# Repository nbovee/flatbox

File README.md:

# Flatbox: Low profile hitbox-layout fightstick

This repository contains 3D-printable models, PCB design files and code needed to make an arcade controller that looks like this:

There are five major versions of the Flatbox. As this is a fork, the three I do not have modifications planned for have been dropped, find them [here](https://github.com/jfedor2/flatbox). They all use Kailh low profile (choc v1) mechanical keyboard switches. The table below lists their main features. See the README for each version for details on how to make them.

version | [rev4](rev4b-pcb) | [rev5B](rev5b-pcb)
------- | --------------------- | ---------------------
case dimensions | 218x130x10mm | 218x126x10mm
compatibility (using provided firmware) | PC, PS3 | PC, PS3
add-on board | - | [RP2040-Zero](https://www.waveshare.com/rp2040-zero.htm)
onboard chip | RP2040 | - 
port | USB-C | USB-C
SMT assembly required | yes | no
firmware | [RP2040](firmware-rp2040) | [RP2040](firmware-rp2040)

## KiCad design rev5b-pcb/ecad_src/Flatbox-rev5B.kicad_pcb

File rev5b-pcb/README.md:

# Flatbox rev5B

This is rev5B of the Flatbox. In this version an [RP2040-Zero](https://www.waveshare.com/rp2040-zero.htm) board is soldered onto the main PCB.
In this version L3 & R3 have been relocated to allow for usage during play (bindable macro's like MK+HK, burst, taunt, etc). 

To make one you will need:

* [3D printed case parts](../case-manufacturing-files) - Select a top and bottom. Two colors tops are available if you have a capable printer.
* [the Flatbox 5B PCB](manufacturing-files)

* [RP2040-Zero](https://www.waveshare.com/rp2040-zero.htm)

* 12-14x Kailh low profile (choc v1) switches of your choice
* (optionally) 12x Kailh low profile hotswap sockets
* [3D printed buttoncaps](../manufacturing-files/3d-printed-buttoncaps)
* 4-6x 6x6x5mm tact switches

* 7x M3x6 flat head screws
* some kind of rubber feet or non-slip padding for the bottom
* a soldering iron

I printed the case at 0.20mm layer height. The top part should be printed upside-down, the bottom part should be printed as-is. They don't require supports.

The PCB can be ordered from a number of online services using the included [Gerber files](manufacturing-files), I used [JLCPCB](https://jlcpcb.com/) (leave all the settings at default, you can choose the PCB color). PCB thickness should be 1.6mm.

The switches can be soldered in directly to the PCB or you can use hotswap sockets. If you want to use hotswap sockets, you will have to print the appropriate bottom part of the case (it's 1mm thicker).

Solder the jumpers for L3 & R3 at the locations they will be used (jumpers are located on the rear of the board).

For the firmware you probably want to use [GP2040-CE](https://gp2040-ce.info/). Go to the [GP2040-CE downloads page](https://gp2040-ce.info/#/download) and get the UF2 file for Flatbox rev5. Do not get the file for the Waveshare RP2040-Zero, even though your stick uses it (it has a different pinout).

To flash the firmware, connect the board to a computer with a USB cable, then press the RESET button while holding the BOOT button on the RP2040-Zero. A drive named "RPI-RP2" should appear. Copy the UF2 file you downloaded to that drive. That's it.

(Of course you can also use any other RP2040-compatible firmware if you want.)

To flash the firmware, connect the board to a computer with a USB cable, then press the RESET button while holding the BOOT button on the RP2040-Zero. A drive named "RPI-RP2" should appear. Copy the [flatbox-rev5.uf2](firmware/flatbox-rev5.uf2) file to that drive. That's it.

PCB design licensed under [CC BY-SA 4.0](https://creativecommons.org/licenses/by-sa/4.0/).

PCB design uses the following:

* [keyswitches.pretty](https://github.com/daprice/keyswitches.pretty) by [daprice](https://github.com/daprice) ([CC BY-SA 4.0](https://creativecommons.org/licenses/by-sa/4.0/))
* RP2040-Zero STEP file downloaded from [Waveshare wiki](https://www.waveshare.com/wiki/RP2040-Zero)

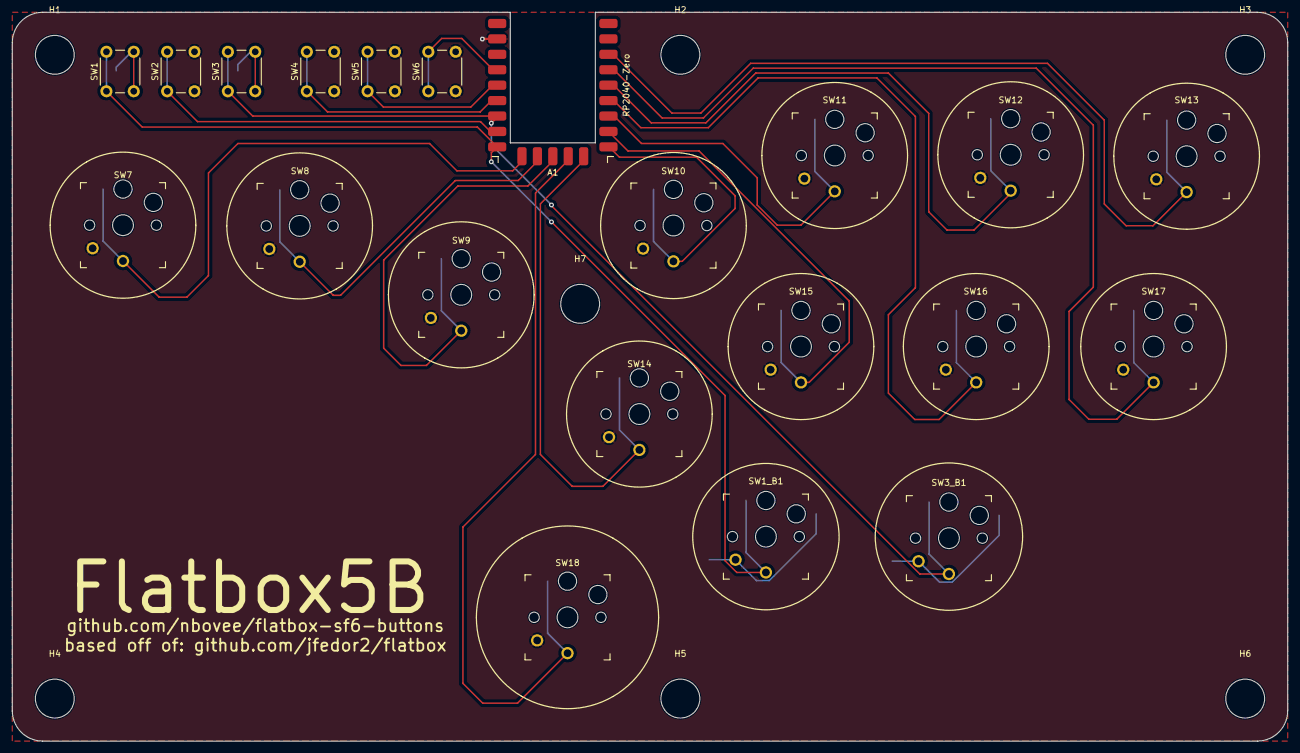
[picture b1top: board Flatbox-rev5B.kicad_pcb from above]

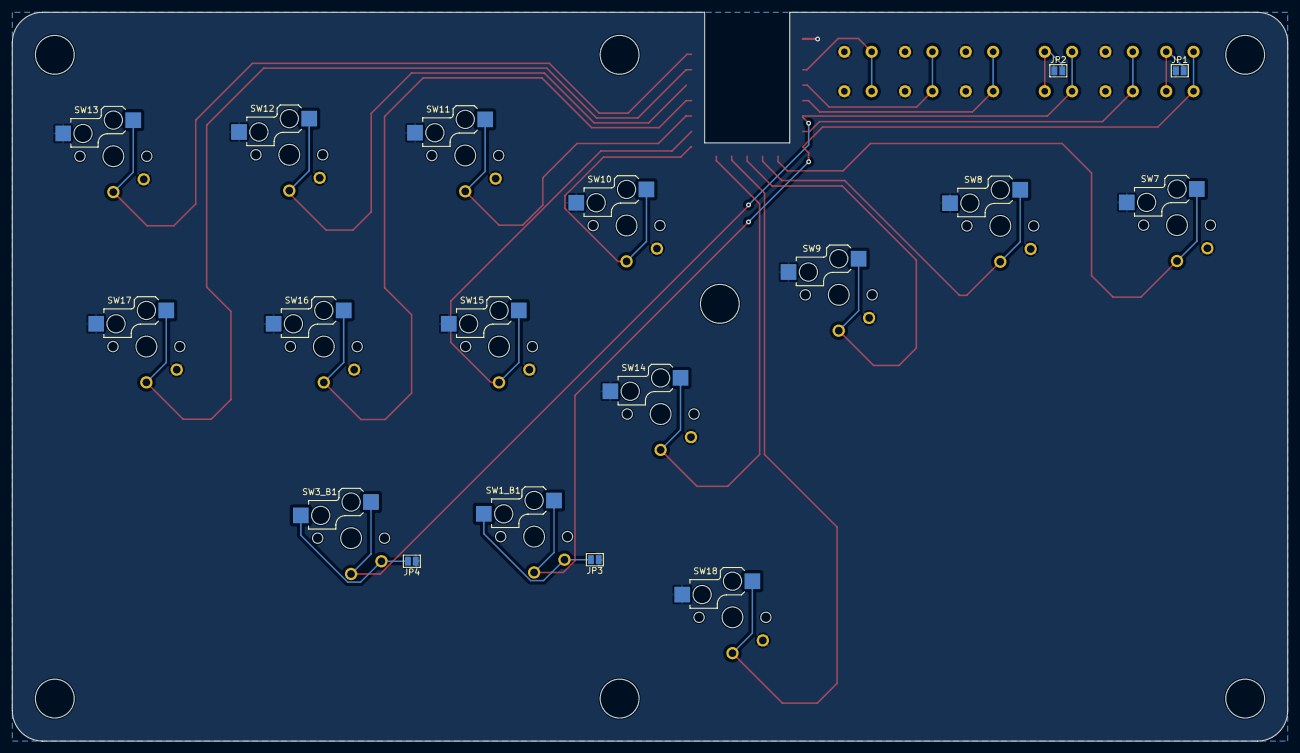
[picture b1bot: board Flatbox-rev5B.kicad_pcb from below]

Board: 2 copper layers, 210.0 x 120.0 mm, 32 parts (4 on the bottom side), 23 nets.

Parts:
A1: RP2040-Zero
H1, H2, H3, H4, H5, H6, H7: MountingHole; MountingHole_6.4mm_M6
JP1: SW1_JP; SolderJumper-2_P1.3mm_Open_Pad1.0x1.5mm
JP2: SW3_JP; SolderJumper-2_P1.3mm_Open_Pad1.0x1.5mm
JP3: SW1B_JP; SolderJumper-2_P1.3mm_Open_Pad1.0x1.5mm
JP4: SW3B_JP; SolderJumper-2_P1.3mm_Open_Pad1.0x1.5mm
SW1, SW2, SW3, SW4, SW5, SW6: SW_Push; SW_PUSH_6mm_H5mm
SW1_B1, SW3_B1, SW7, SW8, SW9, SW10, SW11, SW12, SW13, SW14, SW15, SW16, SW17, SW18: SW_Push; Kailh_socket_PG1350_optional

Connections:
CIRCLE: A1.8 (GPIO7), SW15.1
CROSS: A1.10 (GPIO9), SW14.1
DOWN: A1.13 (GPIO12), SW8.1
GND: A1.23 (GND), JP1.1 (A), JP2.1 (A), JP3.1 (A), JP4.1 (A), SW2.2, SW4.2, SW5.2, SW6.2, SW7.2, SW8.2, SW9.2, SW10.2, SW11.2, SW12.2, SW13.2, SW14.2, SW15.2, SW16.2, SW17.2, SW18.2
HOME: A1.19 (GPIO28), SW5.1
L1: A1.3 (GPIO2), SW13.1
L2: A1.4 (GPIO3), SW17.1
L3: A1.15 (GPIO14), SW1.1, SW1_B1.1
LEFT: A1.14 (GPIO13), SW7.1
unnamed: JP1.2 (B), SW1.2
unnamed: JP2.2 (B), SW3.2
unnamed: JP3.2 (B), SW1_B1.2
unnamed: JP4.2 (B), SW3_B1.2
OPT2: A1.16 (GPIO15), SW2.1
R1: A1.5 (GPIO4), SW12.1
R2: A1.6 (GPIO5), SW16.1
R3: A1.17 (GPIO26), SW3.1, SW3_B1.1
RIGHT: A1.12 (GPIO11), SW9.1
SELECT: A1.18 (GPIO27), SW4.1
SQUARE: A1.9 (GPIO8), SW10.1
START: A1.20 (GPIO29), SW6.1
TRIANGLE: A1.7 (GPIO6), SW11.1
UP: A1.11 (GPIO10), SW18.1

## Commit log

2023-08-11 5B pcb changes
2023-08-11 add note about extra switches
2023-08-11 rev 5B for additional buttons during play
2023-08-11 fix readme
2023-08-11 Rev 5 b (#1)
    * 5B pcb changes
    * add note about extra switches
    * 5B case changes and reorg
    * fix readme
2023-08-11 drop files from rev5 folder, swap Readme
2023-08-11 Rev 5 b (#2)
    * 5B folder with pcb and case changes
    * updated Readme
2023-08-11 drop incorrect files
2023-08-13 add color regions to new case tops
2023-08-13 drop versions I dont want to support
2023-08-13 drop zip in favor of inclusion of project files
2023-08-13 revise readme for fork
2023-08-13 drop rev5
2023-08-13 drop atmega
2023-08-13 update readme for stub
2023-08-13 reorg
2023-08-13 update attribution to fork
2023-08-13 expose kicad files for versioning
2023-08-13 note about two color case
2023-08-13 reflect stated license in repo format
2023-08-13 drop license from root, it applies to PCB only
2023-08-13 rm backups that snuck in
2023-08-13 correct gitignore pattern
2023-08-13 fix table
2023-08-13 add manufacturing files
2023-08-30 5B update
2023-08-30 drop 4B until updated
2023-08-30 drop 2 color case until I can push the correct stl
2023-08-30 drop firmware to match upstream
2023-08-30 rev image
2023-08-30 savepoint
2023-08-30 redirect firmware
